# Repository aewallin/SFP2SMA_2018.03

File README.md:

# SFP-2-SMA Board, 2018-03

This is a simple board for opto/electric and electro/optic conversion of RF-signals (up to maybe 500 MHz)
using telecom SFP transcievers. The board can be fitted with either BNC or SMA connectors. It has one input
which modulates the TX pins of the SFP, and two identical outputs that represent the signal on the RX pins
of the SFP.

Some notes from 2018-04: http://www.anderswallin.net/2018/04/500-mhz-sfp-board-v4/

## Circuit description

Differential (100 Ohm) signals on the TX+/TX- and RX+/RX- pins of the SFP are converted to
single-ended (50 Ohm) signals using Mini-Circuits ADT2-1T transformers.
LMH6702 op-amps amplify/buffer all signals.
LT1963 and LT3015 low-noise LDOs provide +3V3, +6V, and -6V DC rails.
The +3V3 LDO needs heat-sinking, especially with long-range SFPs that have high current draw.

## Links to other SFP-boards

- https://osmocom.org/projects/misc-hardware/wiki/Sfp-experimenter
- https://osmocom.org/projects/misc-hardware/wiki/Sfp-breakout
- https://vksdr.com/pmod

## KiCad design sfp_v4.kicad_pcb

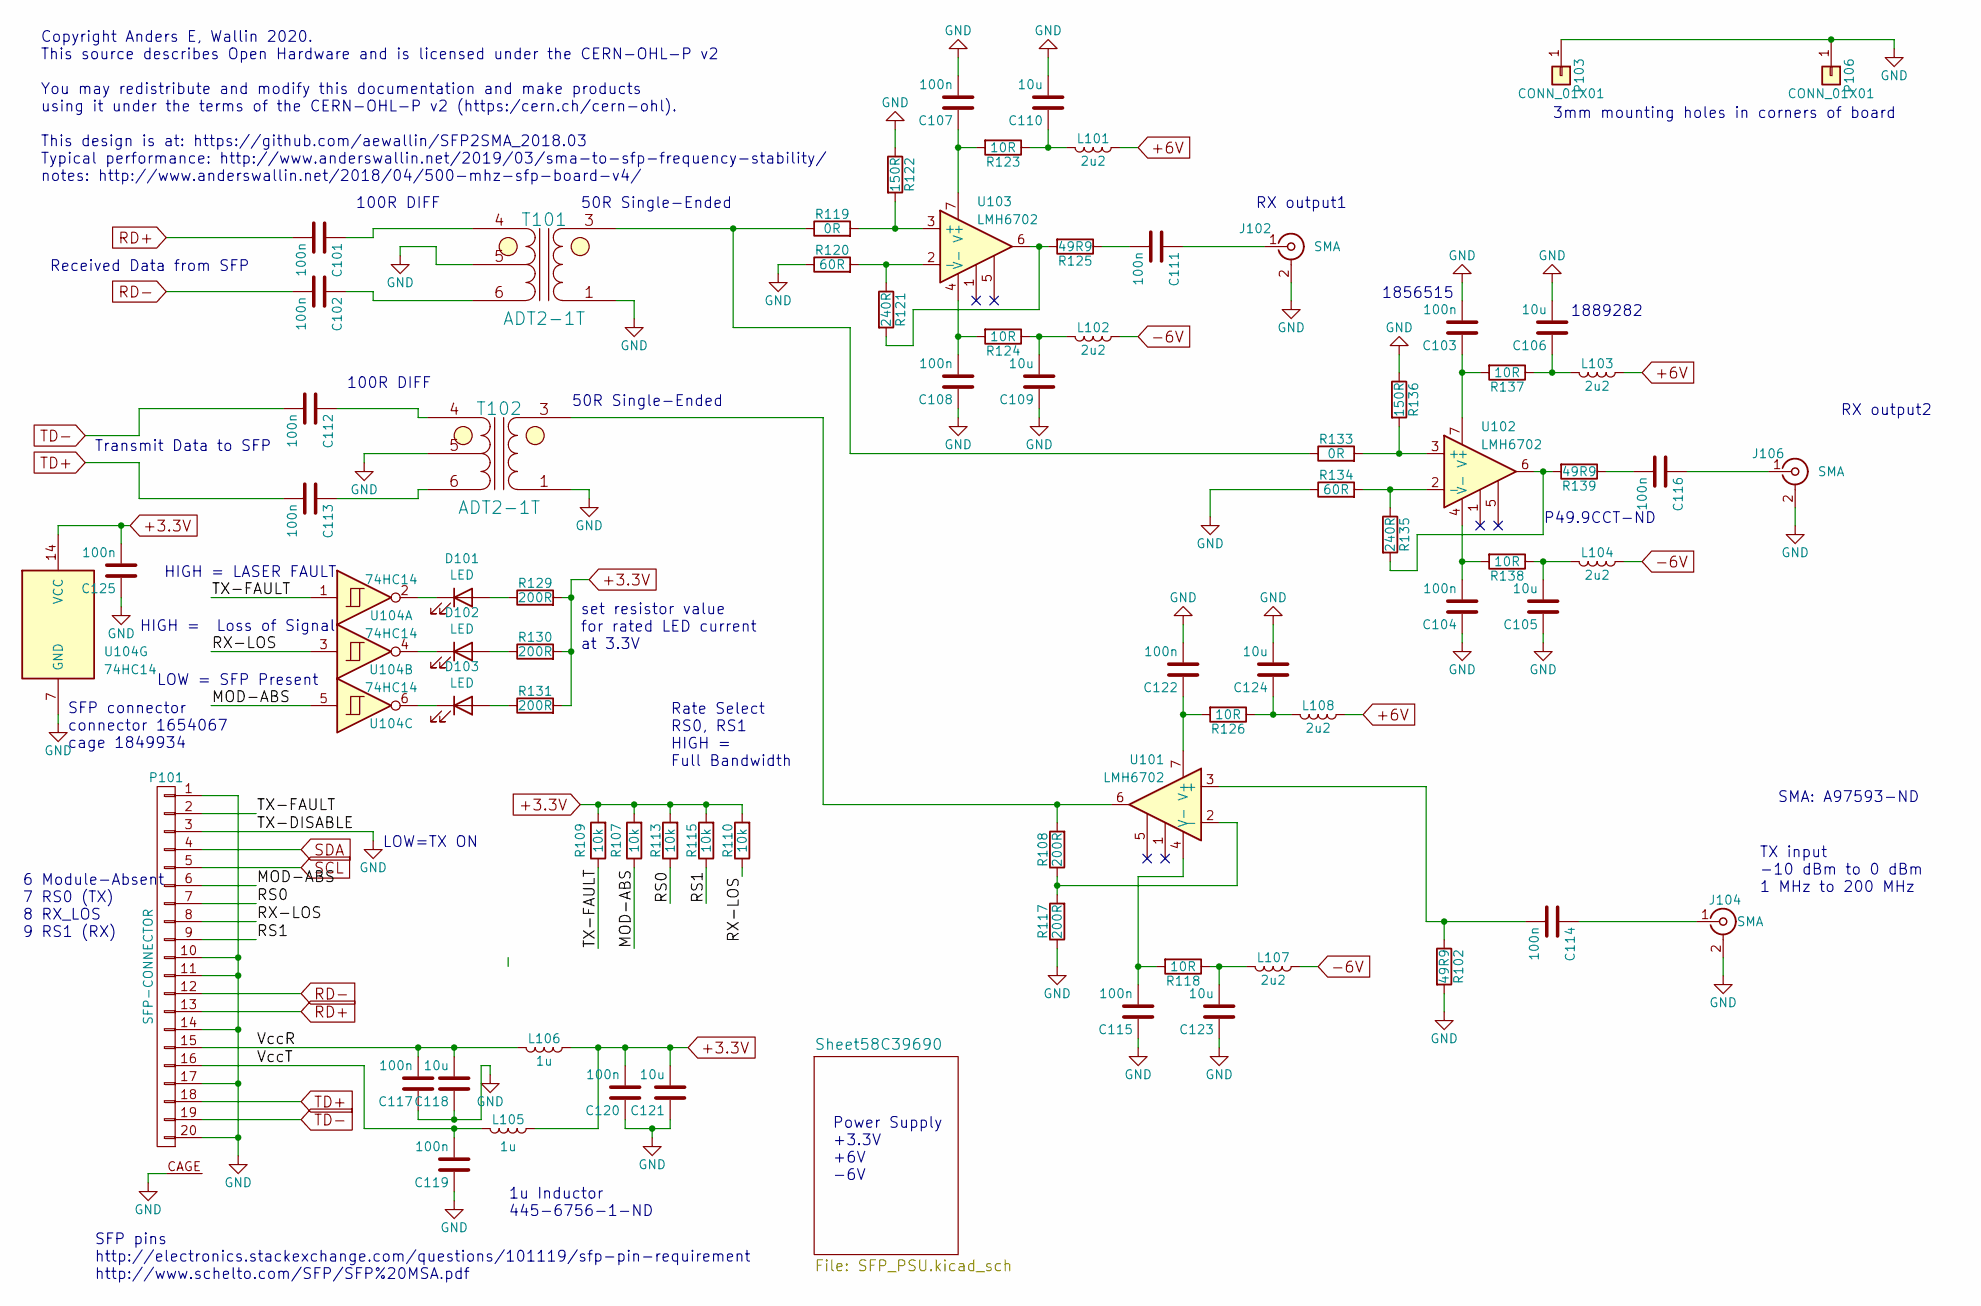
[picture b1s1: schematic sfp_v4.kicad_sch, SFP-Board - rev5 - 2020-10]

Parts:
C101, C102, C103, C104, C107, C108, C111, C112, C113, C114, C115, C116, C117, C119, C120, C122: 100n; C_0805
C105, C106, C109, C110, C118, C121, C123, C124: 10u; C_0805
C125: 100n; C_0805_2012Metric
D101, D102, D103: LED; LED_0805_2012Metric
J102, J104, J106: SMA; SMA_Molex_73251-2200_Horizontal
L101, L102, L103, L104, L107, L108: 2u2; R_0805
L105, L106: 1u; R_0805
P101: SFP-CONNECTOR; Connector_SFP_and_Cage
P103, P106: CONN_01X01; MountingHole_3mm
R102, R125, R139: 49R9; R_0805
R107, R109, R110, R113, R115: 10k; R_0805
R108, R117: 200R; R_0805
R118, R123, R124, R126, R137, R138: 10R; R_0805
R119, R133: 0R; R_0805
R120, R134: 60R; R_0805
R121, R135: 240R; R_0805
R122, R136: 150R; R_0805
R129, R130, R131: 200R; R_0805_2012Metric
T101, T102: ADT2-1T; MiniCircuits_CD542
U101, U102, U103: LMH6702; SOIC-8_3.9x4.9mm_Pitch1.27mm
U104: 74HC14; TSSOP-14_4.4x5mm_P0.65mm

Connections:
+3.3V: C120.2, C121.2, C125.2, L105.1, L106.1, R107.2, R109.2, R110.2, R113.2, R115.2, R129.2, R130.2, R131.2, U104.14 (VCC); also elsewhere on the board
+6V: L101.1, L103.1, L108.1; also elsewhere on the board
-6V: L102.1, L104.1, L107.1; also elsewhere on the board
/MOD-ABS: P101.6, R107.1, U104.5
/RS0: P101.7, R113.1
/RS1: P101.9, R115.1
/RX-LOS: P101.8, R110.1, U104.3
/TX-FAULT: P101.2, R109.1, U104.1
/VccR: C117.2, C118.2, L106.2, P101.15
/VccT: C119.2, L105.2, P101.16
GND: C103.2, C104.1, C105.1, C106.2, C107.2, C108.1, C109.1, C110.2, C115.1, C117.1, C118.1, C119.1, C120.1, C121.1, C122.2, C123.1, C124.2, C125.1, J102.2 (Ext), J104.2 (Ext), J106.2 (Ext), P101.1, P101.3, P101.10, P101.11, P101.14, P101.17, P101.20, P101.CAGE, P103.1, P106.1, R102.2, R117.1, R120.1, R122.1, R134.1, R136.1, T101.1 (PR), T101.5 (SEC_CT), T102.1 (PR), T102.5 (SEC_CT), U104.7 (GND); also elsewhere on the board
unnamed: C101.1, T101.4 (SEC_DOT)
unnamed: C102.1, T101.6 (SEC)
unnamed: C103.1, R137.2, U102.7 (V+)
unnamed: C104.2, R138.2, U102.4 (V-)
unnamed: C105.2, L104.2, R138.1
unnamed: C106.1, L103.2, R137.1
unnamed: C107.1, R123.2, U103.7 (V+)
unnamed: C108.2, R124.2, U103.4 (V-)
unnamed: C109.2, L102.2, R124.1
unnamed: C110.1, L101.2, R123.1
unnamed: C111.1, J102.1 (In)
unnamed: C111.2, R125.1
unnamed: C112.1, T102.4 (SEC_DOT)
unnamed: C113.1, T102.6 (SEC)
unnamed: C114.1, J104.1 (In)
unnamed: C114.2, R102.1, U101.3 (+)
unnamed: C115.2, R118.2, U101.4 (V-)
unnamed: C116.1, J106.1 (In)
unnamed: C116.2, R139.1
unnamed: C122.1, R126.2, U101.7 (V+)
unnamed: C123.2, L107.2, R118.1
unnamed: C124.1, L108.2, R126.1
unnamed: D101.1 (K), U104.2
unnamed: D101.2 (A), R129.1
unnamed: D102.1 (K), U104.4
unnamed: D102.2 (A), R130.1
unnamed: D103.1 (K), U104.6
unnamed: D103.2 (A), R131.1
unnamed: R108.1, R117.2, U101.2 (-)
unnamed: R108.2, T102.3 (PR_DOT), U101.6
unnamed: R119.1, R133.1, T101.3 (PR_DOT)
unnamed: R119.2, R122.2, U103.3 (+)
unnamed: R120.2, R121.1, U103.2 (-)
unnamed: R121.2, R125.2, U103.6
unnamed: R133.2, R136.2, U102.3 (+)
unnamed: R134.2, R135.1, U102.2 (-)
unnamed: R135.2, R139.2, U102.6
RD+: C101.2, P101.13
RD-: C102.2, P101.12
SCL: P101.5
SDA: P101.4
TD+: C113.2, P101.18
TD-: C112.2, P101.19

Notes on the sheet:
100R DIFF
RX output2
1889282
P49.9CCT-ND
HIGH = LASER FAULT
LOW = SFP Present
Transmit Data to SFP
RX output1
SFP connector connector 1654067 cage 1849934
Received Data from SFP
Power Supply +3.3V +6V -6V
50R Single-Ended
Rate Select RS0, RS1 HIGH = Full Bandwidth
6 Module-Absent 7 RS0 (TX) 8 RX_LOS 9 RS1 (RX)
SFP pins http://electronics.stackexchange.com/questions/101119/sfp-pin-requirement http://www.schelto.com/SFP/SFP%20MSA.pdf
1u Inductor 445-6756-1-ND
HIGH = Loss of Signal
LOW=TX ON
Copyright Anders E, Wallin 2020. This source describes Open Hardware and is licensed under the CERN-OHL-P v2 You may redistribute and modify this documentation and make products using it under the terms of the CERN-OHL-P v2 (https:/cern.ch/cern-ohl). This design is at: https://github.com/aewallin/S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
set resistor value for rated LED current at 3.3V
SMA: A97593-ND
1856515
TX input -10 dBm to 0 dBm 1 MHz to 200 MHz
3mm mounting holes in corners of board

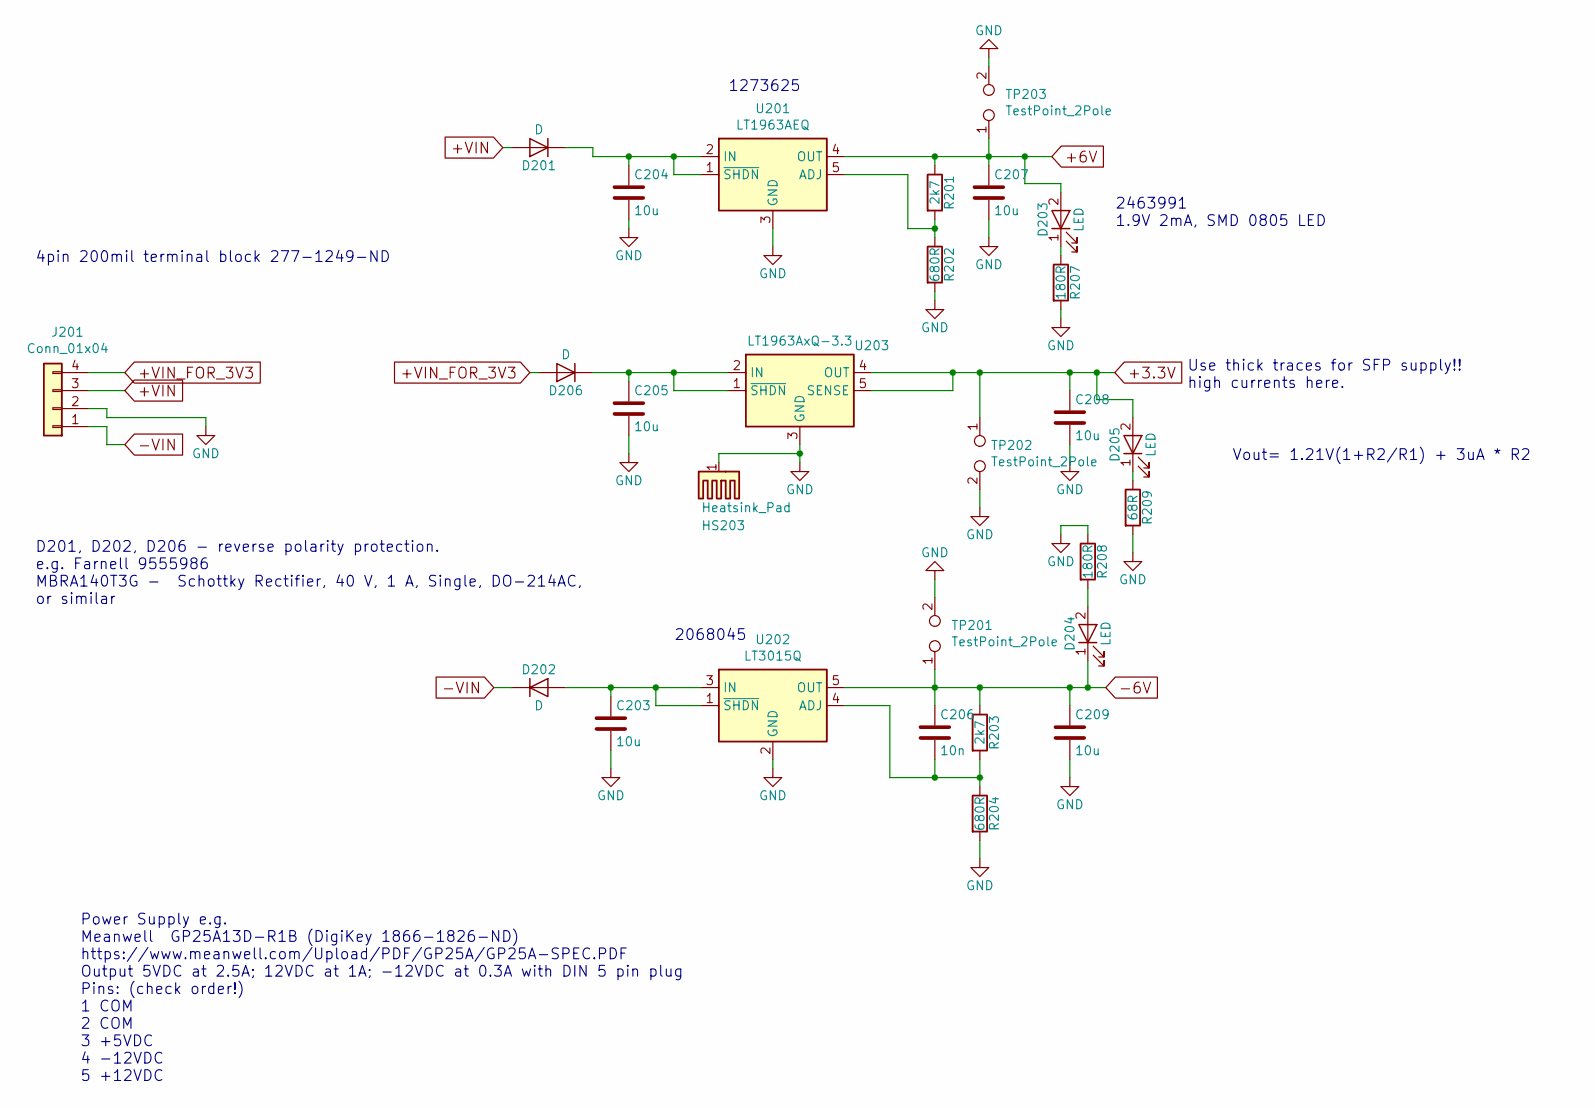
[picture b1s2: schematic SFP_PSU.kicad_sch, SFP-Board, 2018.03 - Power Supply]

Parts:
C203, C204, C205, C207, C208, C209: 10u; C_0805
C206: 10n; C_0805
D201, D202, D206: D; DIODE_DO-214BA
D203, D204, D205: LED; LED_0805
HS203: Heatsink_Pad; Heatsink_Fischer_FK24413D2PAK_26x13mm
J201: Conn_01x04; TerminalBlock_bornier-4_P5.08mm
R201, R203: 2k7; R_0805
R202, R204: 680R; R_0805
R207, R208: 180R; R_0805
R209: 68R; R_0805
TP201, TP202, TP203: TestPoint_2Pole; TestPoint_2Pads_Pitch2.54mm_Drill0.8mm
U201: LT1963AEQ; TO-263-5_TabPin3
U202: LT3015Q; TO-263-5_TabPin3
U203: LT1963AxQ-3.3; TO-263-5_TabPin3

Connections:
+3.3V: C208.1, D205.2 (A), TP202.1, U203.4 (OUT), U203.5 (SENSE); also elsewhere on the board
+6V: C207.1, D203.2 (A), R201.1, TP203.1, U201.4 (OUT); also elsewhere on the board
+VIN: D201.2 (A), J201.3
+VIN_FOR_3V3: D206.2 (A), J201.4
-6V: C206.1, C209.1, D204.1 (K), R203.1, TP201.1, U202.5 (OUT); also elsewhere on the board
-VIN: D202.1 (K), J201.1
GND: C203.2, C204.2, C205.2, C207.2, C208.2, C209.2, HS203.1, J201.2, R202.2, R204.2, R207.2, R208.1, R209.2, TP201.2, TP202.2, TP203.2, U201.3 (GND), U202.2 (GND), U203.3 (GND); also elsewhere on the board
unnamed: C203.1, D202.2 (A), U202.1 (~SHDN), U202.3 (IN)
unnamed: C204.1, D201.1 (K), U201.1 (~SHDN), U201.2 (IN)
unnamed: C205.1, D206.1 (K), U203.1 (~SHDN), U203.2 (IN)
unnamed: C206.2, R203.2, R204.1, U202.4 (ADJ)
unnamed: D203.1 (K), R207.1
unnamed: D204.2 (A), R208.2
unnamed: D205.1 (K), R209.1
unnamed: R201.2, R202.1, U201.5 (ADJ)

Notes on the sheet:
Vout= 1.21V(1+R2/R1) + 3uA * R2
2068045
Power Supply e.g. Meanwell GP25A13D-R1B (DigiKey 1866-1826-ND) https://www.meanwell.com/Upload/PDF/GP25A/GP25A-SPEC.PDF Output 5VDC at 2.5A; 12VDC at 1A; -12VDC at 0.3A with DIN 5 pin plug Pins: (check order!) 1 COM 2 COM 3 +5VDC 4 -12VDC 5 +12VDC
D201, D202, D206 - reverse polarity protection. e.g. Farnell 9555986 MBRA140T3G - Schottky Rectifier, 40 V, 1 A, Single, DO-214AC, or similar
2463991 1.9V 2mA, SMD 0805 LED
1273625
4pin 200mil terminal block 277-1249-ND
Use thick traces for SFP supply!! high currents here.

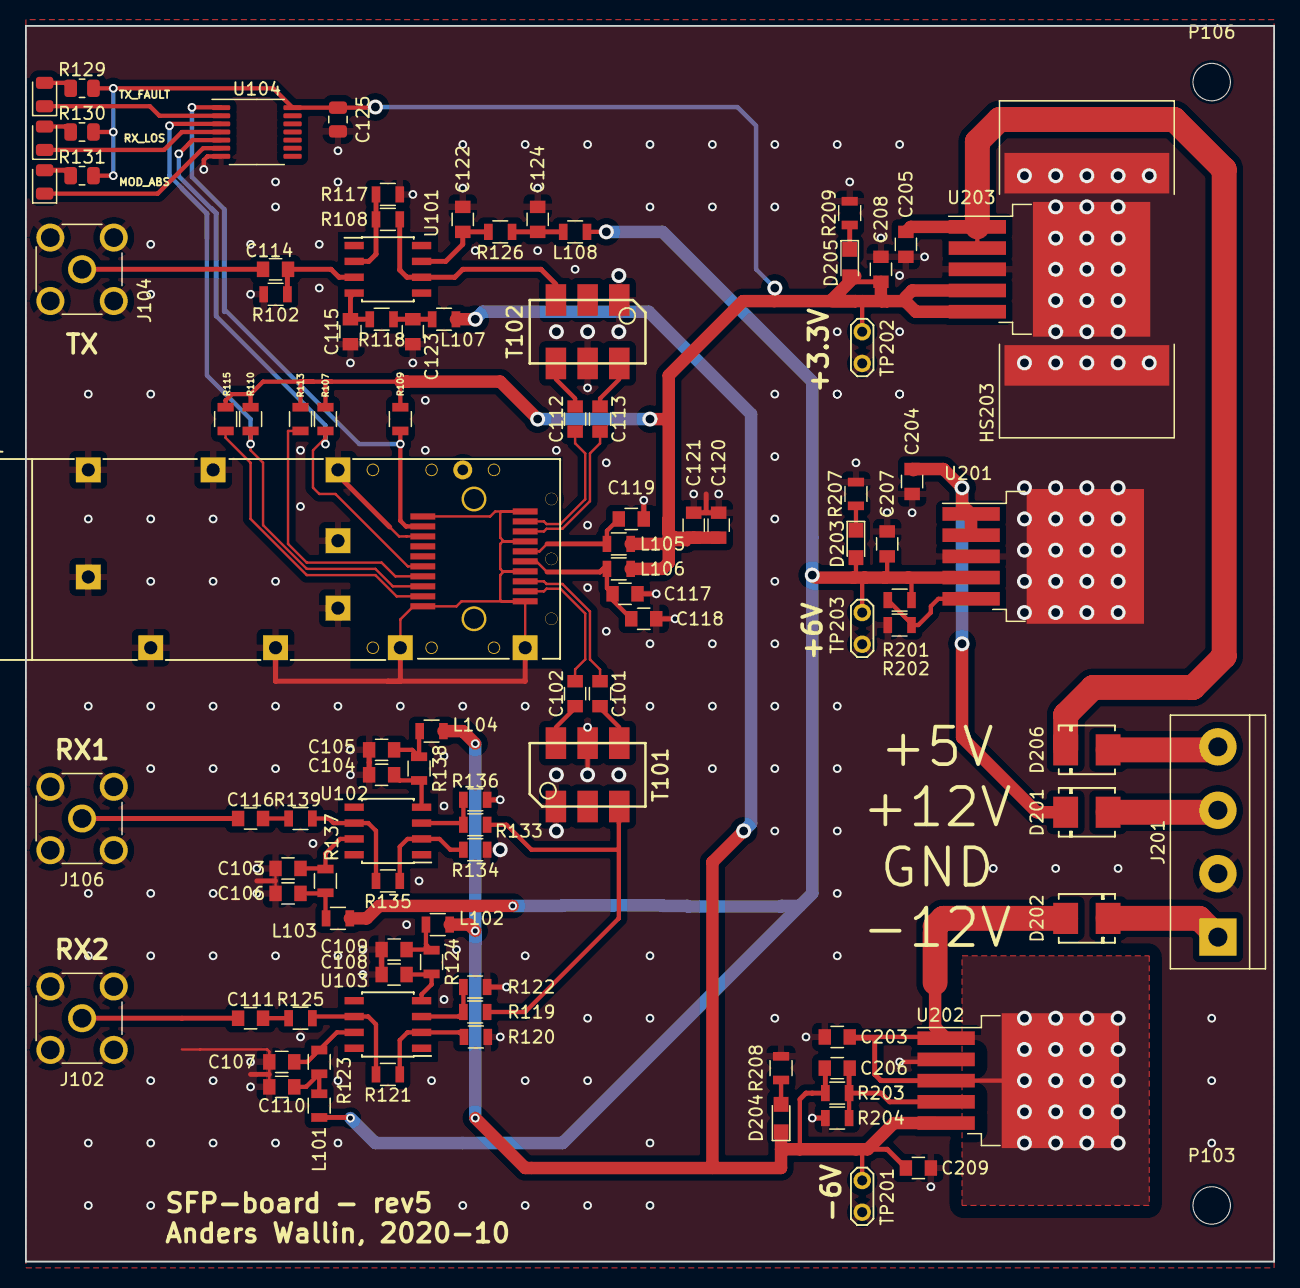
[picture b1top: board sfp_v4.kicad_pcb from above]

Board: 2 copper layers, 100.0 x 99.0 mm, 103 parts (0 on the bottom side), 63 nets.

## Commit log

2018-10-24 initial commit of sfp2sma design
2018-10-24 rotate SCH pdf
2019-03-25 osmocom sfp board links
2019-05-25 add missing component values and comments to schematic
2020-10-22 revise: kicad standard lib symbols/footprints, add SFP status LEDs
2020-10-23 add BOM
2020-10-25 simplify
2020-10-27 psu?
2020-10-27 revise
2020-10-28 adjust bom
2020-10-29 tune component values
2020-10-31 minor tuning
2020-11-01 add link
2020-11-28 bump gain to 1+240/60
2020-12-01 adjust values
2022-12-03 kicad6 version
2022-12-03 remove kicad5 files
2025-10-22 update to kicad 9
2025-10-22 silk mods
